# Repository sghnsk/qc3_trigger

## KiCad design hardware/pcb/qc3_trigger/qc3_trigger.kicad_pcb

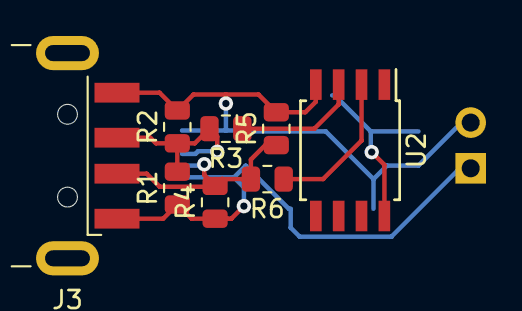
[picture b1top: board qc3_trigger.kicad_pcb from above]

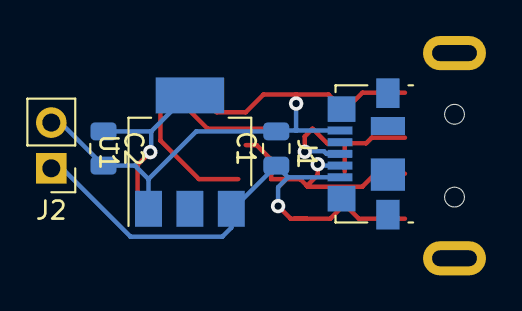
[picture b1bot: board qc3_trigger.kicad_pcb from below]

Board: 2 copper layers, 13 parts (5 on the bottom side), 7 nets.

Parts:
C1, C2: 100n; C_0805_2012Metric
J1: USB_B_Micro; USB_Micro-B_Molex_47346-0001
J2: Vout; PinHeader_1x02_P2.54mm_Vertical
J3: USB_A; USB_A_CNCTech_1001-011-01101_Horizontal
R1, R4: 10k; R_0805_2012Metric
R2, R5: 1k5; R_0805_2012Metric
R3, R6: 470; R_0805_2012Metric
U1: AMS1117-5.0; SOT-223-3_TabPin2
U2: ATtiny85V-10SU; SOIJ-8_5.3x5.3mm_P1.27mm

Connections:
+5V: C1.1, J1.1, J2.1, J3.1, R1.1, R4.1, U1.3
GND: C1.2, C2.2, J1.5, J2.2, J3.4, R2.2, R5.2, U1.1, U2.4
unnamed: C2.1, U1.2, U2.8
unnamed: J1.2, J3.2, R4.2, R5.1, R6.2
unnamed: J1.3, J3.3, R1.2, R2.1, R3.2
unnamed: R3.1, U2.3
unnamed: R6.1, U2.2

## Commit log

2021-09-16 Начало работы с платой
2021-09-16 Поменял местами пины dpin, dmpin
2021-09-16 Переместил в папку hardware
2021-09-16 добавил gitignore
2021-09-16 правки в схеме
2021-09-16 первые наброски платы
2021-09-16 автодобавление перевода строки
2021-09-16 удалил qc3control из lib
    используется из libdeps
2021-09-16 поменял местами dppin и dnpin
2021-09-16 наброски разводки и компановки на плате
2021-09-16 моделька корпуса usb a male разъема
2021-09-22 вариант с повернутой тинькой
